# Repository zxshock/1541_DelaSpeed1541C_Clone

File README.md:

Done in 2017, based on a historic PCB I managed to obtain. Needs additional SpeedDOS style parallel cable between C64 and 1541.
Sadly we never found the corresponding C64 Kernal - if my memory serves me right, this also works with "SpeedDOS Pro" ROMs.

Documentation is a mess - as usual. Uploaded completely "as is", since I lost all interest in the Commodore community.
Uploaded for your personal enjoyment. If I see this advertised as "r@r3 l@@k - high quality Repro of a long lost expansion!!!!!!11one" for 50€+ on eBay I sincerely hope you're getting the customers you deserve :)

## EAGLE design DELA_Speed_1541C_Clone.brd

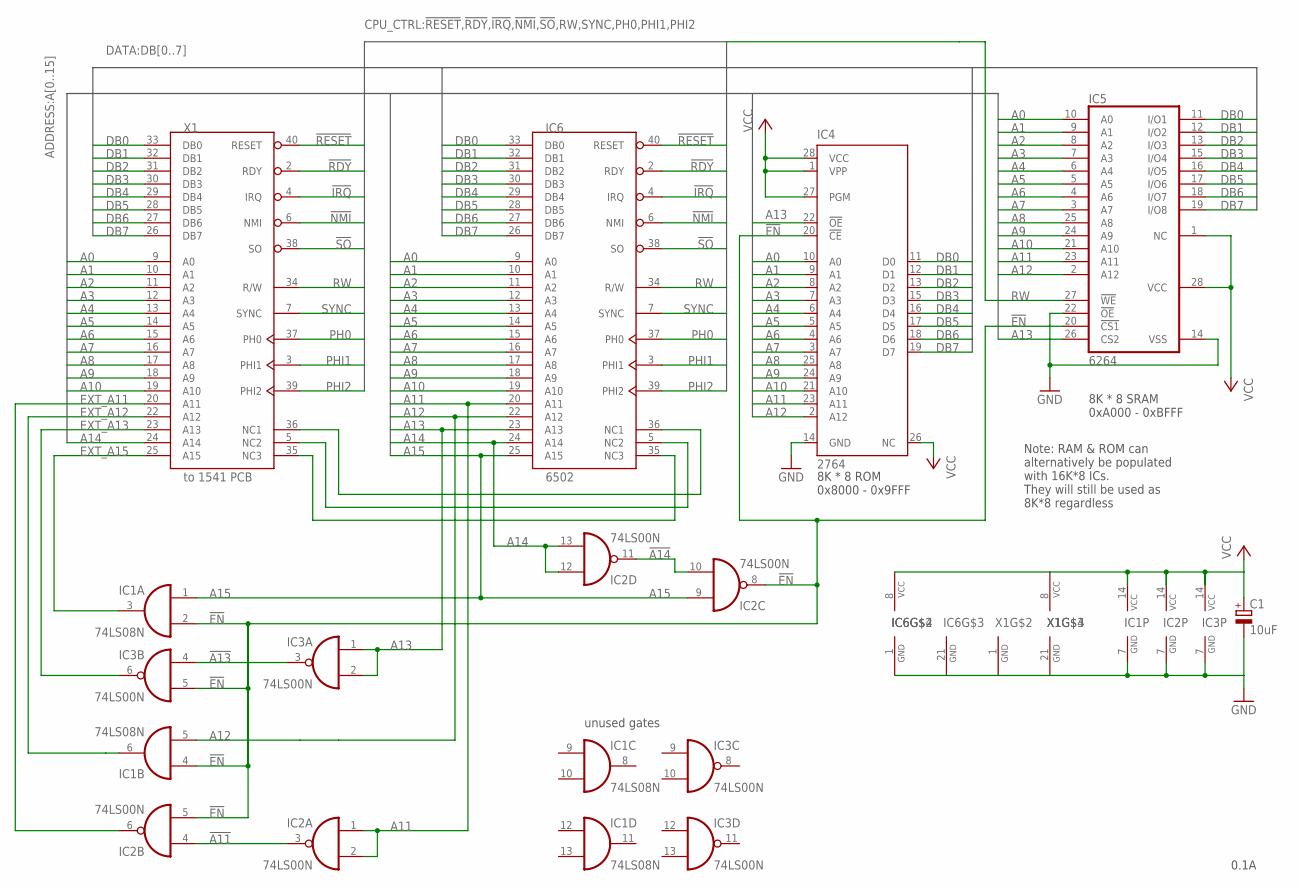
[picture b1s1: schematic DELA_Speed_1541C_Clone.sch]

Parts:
C1: 10uF; E2,5-6
IC1: 74LS08N; DIL14
IC2, IC3: 74LS00N; DIL14
IC4: 2764; DIL28-6
IC5: 6264; DIL28-6
IC6: 6502; DIP40
X1: to 1541 PCB; DIP40

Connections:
!A11: IC2.3 (O), IC2.4 (I0)
!A13: IC3.3 (O), IC3.4 (I0)
!A14: IC2.10 (I1), IC2.11 (O)
!EN: IC1.2 (I1), IC1.4 (I0), IC2.5 (I1), IC2.8 (O), IC3.5 (I1), IC4.20 (!CE), IC5.20 (!CS1)
!IRQ: IC6.4 (IRQ), X1.4 (IRQ)
!NMI: IC6.6 (NMI), X1.6 (NMI)
!RDY: IC6.2 (RDY), X1.2 (RDY)
!RESET: IC6.40 (RESET), X1.40 (RESET)
!SO: IC6.38 (SO), X1.38 (SO)
A0: IC4.10 (A0), IC5.10 (A0), IC6.9 (A0), X1.9 (A0)
A1: IC4.9 (A1), IC5.9 (A1), IC6.10 (A1), X1.10 (A1)
A2: IC4.8 (A2), IC5.8 (A2), IC6.11 (A2), X1.11 (A2)
A3: IC4.7 (A3), IC5.7 (A3), IC6.12 (A3), X1.12 (A3)
A4: IC4.6 (A4), IC5.6 (A4), IC6.13 (A4), X1.13 (A4)
A5: IC4.5 (A5), IC5.5 (A5), IC6.14 (A5), X1.14 (A5)
A6: IC4.4 (A6), IC5.4 (A6), IC6.15 (A6), X1.15 (A6)
A7: IC4.3 (A7), IC5.3 (A7), IC6.16 (A7), X1.16 (A7)
A8: IC4.25 (A8), IC5.25 (A8), IC6.17 (A8), X1.17 (A8)
A9: IC4.24 (A9), IC5.24 (A9), IC6.18 (A9), X1.18 (A9)
A10: IC4.21 (A10), IC5.21 (A10), IC6.19 (A10), X1.19 (A10)
A11: IC2.1 (I0), IC2.2 (I1), IC4.23 (A11), IC5.23 (A11), IC6.20 (A11)
A12: IC1.5 (I1), IC4.2 (A12), IC5.2 (A12), IC6.22 (A12)
A13: IC3.1 (I0), IC3.2 (I1), IC4.22 (!OE), IC5.26 (CS2), IC6.23 (A13)
A14: IC2.12 (I0), IC2.13 (I1), IC6.24 (A14), X1.24 (A14)
A15: IC1.1 (I0), IC2.9 (I0), IC6.25 (A15)
DB0: IC4.11 (D0), IC5.11 (I/O1), IC6.33 (DB0), X1.33 (DB0)
DB1: IC4.12 (D1), IC5.12 (I/O2), IC6.32 (DB1), X1.32 (DB1)
DB2: IC4.13 (D2), IC5.13 (I/O3), IC6.31 (DB2), X1.31 (DB2)
DB3: IC4.15 (D3), IC5.15 (I/O4), IC6.30 (DB3), X1.30 (DB3)
DB4: IC4.16 (D4), IC5.16 (I/O5), IC6.29 (DB4), X1.29 (DB4)
DB5: IC4.17 (D5), IC5.17 (I/O6), IC6.28 (DB5), X1.28 (DB5)
DB6: IC4.18 (D6), IC5.18 (I/O7), IC6.27 (DB6), X1.27 (DB6)
DB7: IC4.19 (D7), IC5.19 (I/O8), IC6.26 (DB7), X1.26 (DB7)
EXT_A11: IC2.6 (O), X1.20 (A11)
EXT_A12: IC1.6 (O), X1.22 (A12)
EXT_A13: IC3.6 (O), X1.23 (A13)
EXT_A15: IC1.3 (O), X1.25 (A15)
GND: C1.-, IC1.7 (GND), IC2.7 (GND), IC3.7 (GND), IC4.14 (GND), IC5.14 (VSS), IC5.22 (!OE), IC6.1 (GND), IC6.21 (GND), X1.1 (GND), X1.21 (GND)
NC1: IC6.36 (NC1), X1.36 (NC1)
NC2: IC6.5 (NC2), X1.5 (NC2)
NC3: IC6.35 (NC3), X1.35 (NC3)
PH0: IC6.37 (PH0), X1.37 (PH0)
PHI1: IC6.3 (PHI1), X1.3 (PHI1)
PHI2: IC6.39 (PHI2), X1.39 (PHI2)
RW: IC5.27 (!WE), IC6.34 (R/W), X1.34 (R/W)
SYNC: IC6.7 (SYNC), X1.7 (SYNC)
VCC: C1.+, IC1.14 (VCC), IC2.14 (VCC), IC3.14 (VCC), IC4.1 (VPP), IC4.26 (NC), IC4.27 (PGM), IC4.28 (VCC), IC5.1 (NC), IC5.28 (VCC), IC6.8 (VCC), X1.8 (VCC)

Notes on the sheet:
unused gates
0.1A
8K * 8 SRAM 0xA000 - 0xBFFF
8K * 8 ROM 0x8000 - 0x9FFF
Note: RAM & ROM can alternatively be populated with 16K*8 ICs. They will still be used as 8K*8 regardless

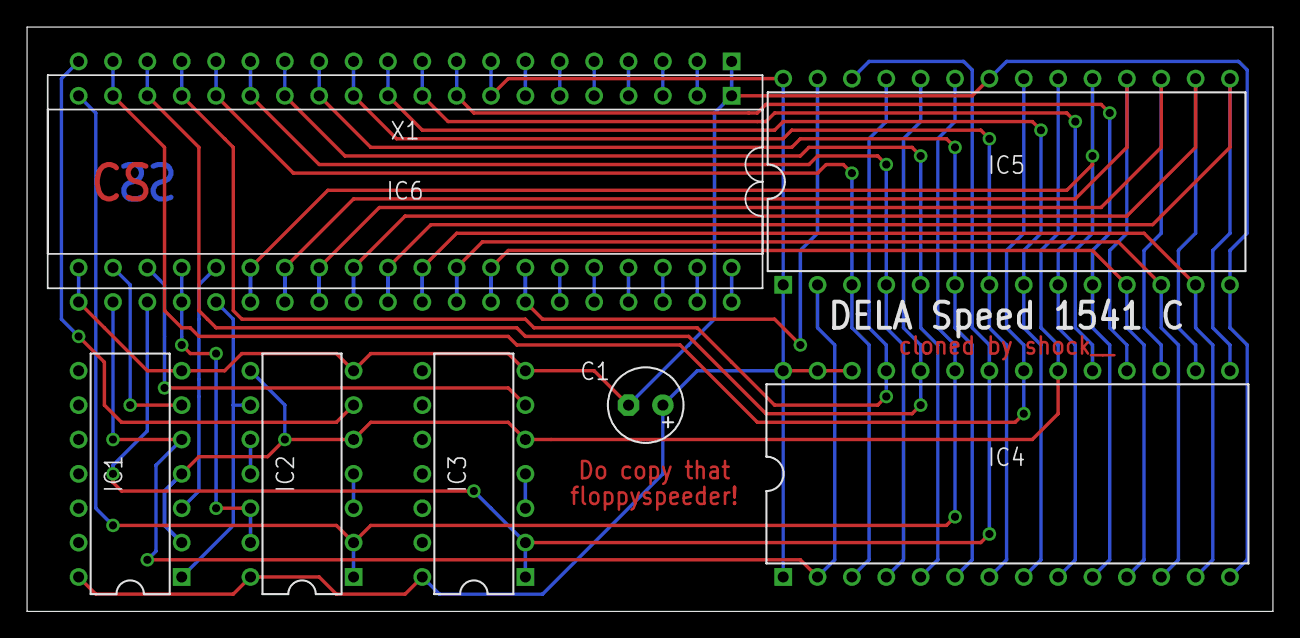
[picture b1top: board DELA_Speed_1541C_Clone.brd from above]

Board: 2 copper layers, 92.1 x 43.2 mm, 8 parts (0 on the bottom side), 47 nets.
